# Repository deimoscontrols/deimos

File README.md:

# Deimos

|[Website](https://deimoscontrols.com) |\||[Control Program](https://github.com/deimoscontrols/deimos/tree/main/software/deimos) |\|| [Packet Formats](https://github.com/deimoscontrols/deimos/tree/main/software/deimos_shared) |\|| [Firmware](https://github.com/deimoscontrols/deimos/tree/main/firmware) |\|| [Hardware Designs](https://github.com/deimoscontrols/deimos/tree/main/hardware) |
|-----------------|-|--------------|-|----------|-|----------|-----|-|

Realtime data acquisition and controls ecosystem, including hardware, firmware, and software.

# Contact

|  | Purpose |
|-------|---------|
| support@deimoscontrols.com <br> or <br>https://deimoscontrols.com/contact/ | Questions about the hardware or software |

# Hardware Peripherals

| Model | I/O Medium | Sample/Control Rate | Input Capabilities | Output Capabilities |
|------|------------|------------|--------------------|---------------------|
| [Deimos DAQ 7.0.x](https://deimoscontrols.com/products/deimos_daq/) | UDP/IP/Ethernet | 5Hz-8kHz measure & control<br>5Hz-500Hz Modbus<br><br>Performance depends on network and host machine | 16x analog, 6x digital | 4x PWM <br>2x analog<br>4x GPIO |
| [Deimos DAQ 8.0.x](https://deimoscontrols.com/products/specs/) | UDP/IP and Modbus/TCP over Ethernet | 5Hz-8kHz measure & control<br>5Hz-500Hz Modbus<br><br>Performance depends on network and host machine | 6x voltage, 2x thermocouple, 3x resistance, 4x 4-20mA<br>2x GPIO, 4x encoder<br>Bus current, bus voltage, and board temperature diagnostics | 4x PWM<br>2x analog<br>4x GPIO |

# Controller Comm. Media

Communication with peripherals is done via message passing on an arbitrary socket. New communication media can be used by implementing the `Socket` trait.

While the controller can accommodate multiple communication media, a peripheral will typically only implement one method for reliability reasons.

| I/O Medium | Notes |
|------------|-------|
| UDP/IPV4 | Nominal peripheral I/O; compared to TCP, eliminates packet storm network instability.<br><br>The controller reasserts the full peripheral state on each cycle, so while UDP allows some packet loss (typically 1e-4 or less), a change in peripheral state is never missed permanently. |
| Unix socket | Inter-process communication option for software peripheral mockups |
| Thread channel | Inter-thread communication option for software peripheral mockups |

Several more socket implementations are planned, including TCP, UDP/IPV6, and thread channel message passing.

# Data Integrations

Data integration implementations perform I/O and database transactions on a separate core to avoid blocking the main control loop, unless no separate core is available.

| Target | I/O Medium | Notes |
|--------|--------|-------|
| CSV    | Disk | Fixed-width row format.<br>Wrap, split, or terminate at end of pre-sized file. |
| DataFrame | RAM | Wrap or terminate at end of preallocated in-memory storage. |
| TimescaleDB (postgres) | TCP or unix socket | Create table & schema or reuse existing.<br>Insert individual rows or write buffered batches for increased total ingestion rate.<br>Set fixed retention duration. |
| Latest-value | RAM | Read the latest data manually from outside the control program. |

# Calculation Functions

| Name | Description | Notes |
|------|-------------|-------|
| Controllers | | |
| SequenceMachine | A flexible state-machine where each state is defined by a time-dependent lookup table sequence with user-defined transition criteria | Allows implementation of essentially arbitrary scheduling and operational logic |
| Pid | Proportion-integral-derivative controller with anti-windup | |
| Hysteretic | Bang-bang controller with persistence counter | |
| Interpolation & Filtering | | |
| Butter | Second-order Butterworth low-pass filter | |
| Polynomial | Fast evaluation of polynomials for calibrations | Includes Levenberg-Marquardt curve-fitting utility |
| Temperature | | |
| TcKtype | K-type thermocouple tables with cold-junction correction | Highly-optimized, low-latency, embedded-compatible implementation based on ITS-90 tables |
| RtdPt100 | 100-ohm platinum RTD temperature-resistance tables | Highly-optimized, low-latency, embedded-compatible implementation based on DIN-43-760 / ITS-90 and IEC 60751 / Callender-Van Dusen |

... in addition to a variety of unremarkable math functions.

# Goals and Anti-Goals

The goals of this ecosystem are:

* Tightly-integrated sensor frontends
* _Fully independent_ input and output channels; every advertised channel is available _at the same time_
* Full reassertion of state at each control cycle; robust to packet loss
* SI-traceable calibrations
* Control program without required root/admin access or drivers
* Run on standard networking hardware with sub-microsecond time sync
* Semantic versioning for both hardware and software to prevent unexpected breaking changes
* 100% end-to-end open-source hardware, firmware, and software under permissive licenses

Notable anti-goals:

* Copyright mongering
* "Internet-of-Things" (IoT) functionality
* Over-the-Air (OTA) firmware updates
* Performative complexity
* Skimping on bits

# Versioning

To prevent unexpected breaking changes, both software and hardware use semantic versioning and, whenever possible, use procedural semver linting to avoid unexpected or unintuitive breakage.

Semantic versioning of hardware is not yet a well-established practice. Here, it is taken to cover both hardware and accompanying firmware, and their interfaces:

* Major version: Potentially breaking changes
    * Examples: Removing a channel, increasing filter phase lag, narrowing samplerate range, or changing packet interchange format, reducing overvoltage tolerance
        * Adding a channel is also a breaking change if it affects packet interchange format
    * Notable non-examples: Changing connector types for sensors without a noise-level or thermoelectric voltage sensitivity, changing model number
* Minor version: Backward-compatible changes
    * Examples: Adding a channel, increasing samplerate range, decreasing filter phase lag, increasing overvoltage tolerance
* Patch version: Forward- and backward- compatible changes
    * Examples: Updating silkscreen, changing non-sensitive connector types, swapping non-sensitive components such as decoupling capacitors

Both major and minor hardware versions are accompanied by new hardware project files. Patch hardware versions are applied to the existing hardware project files.

# License

Licensed under either of

* Apache License, Version 2.0, ([LICENSE-APACHE](LICENSE-APACHE.txt) or http://www.apache.org/licenses/LICENSE-2.0)
* MIT license ([LICENSE-MIT](LICENSE-MIT.txt) or http://opensource.org/licenses/MIT)

at your option.

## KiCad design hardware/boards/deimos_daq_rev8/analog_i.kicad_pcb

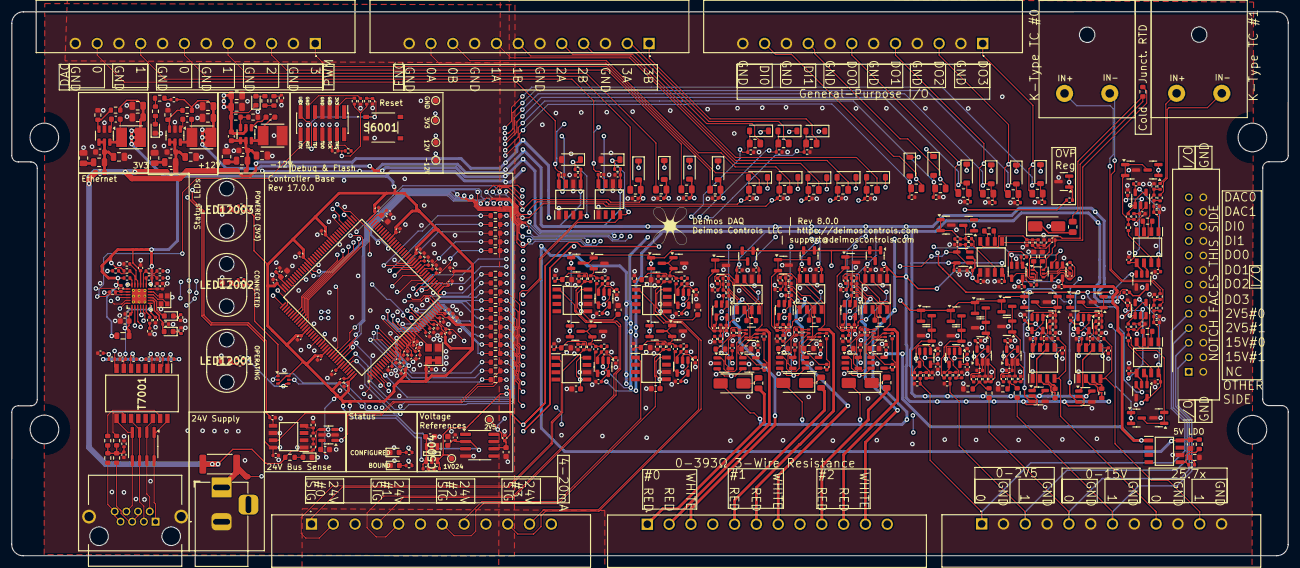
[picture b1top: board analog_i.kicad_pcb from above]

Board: 4 copper layers, 223.0 x 95.0 mm, 582 parts (0 on the bottom side), 312 nets.

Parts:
-1001: logo_minimal_25p4_by_20p3_mm; logo_minimal_12p7_by_10p9_mm
C3003, C10001, C10005, C11002, C11005, C14002, C14005, C14006, C28001, C30001, C32001, C34001: 0.1uF 50V 0603; C_0603_1608Metric
C4001, C4003, C5001, C5003, C9001, C9003, C13001, C13003, C15001, C15003, C17001, C17003: 2.2uF; C_0402_1005Metric
C4002, C5002, C9002, C13002, C15002, C17002: 1uF; C_0402_1005Metric
C4004, C4005, C4007, C4010, C5004, C5007, C5008, C5009, C5010, C6021, C6022, C6024, C6026, C6027, C6028, C6029, C6030, C6031, C6032, C6033, C6034, C6036, C6037, C6038, C6039, C6041, C6043, C6048, C6050, C7005, C7006, C7007, C7008, C7010, C7011, C8002, C8005, C9004, C9005, C13004, C13007, C13010, C15004, C15008, C15009, C16001, C17004, C17007, C17008, C17009, C17010, C18002, C19003, C19004, C21003, C21004, C23001, C24001, C24004, C26001, C27003, C27004, C29003, C29004, C31003, C31004, C33003, C33004, C35003, C35004, C36001, C36002, C37003, C37004, C38001, C38002, C39003, C39004, C41003, C41004, C43003, C43004, C45003, C45004, C47003, C47004, C53001, C53002, C54001, C54002: 0.1uF; C_0402_1005Metric
C4006, C4008, C6023, C6025, C9007, C9008, C11001, C14001, C18001, C22001, C23002, C23003, C26002, C26003: 10nF; C_0402_1005Metric
C5012, C6035, C6040, C6049, C6051, C7009: 10uF; C_0603_1608Metric
C6001, C6002, C6003, C6004, C6005, C6006, C6007, C6008, C6009, C6010, C6011, C6012, C6013, C6016, C6017, C6018, C6019, C6020, C7004: 1uF 0402; C_0402_1005Metric
C7003: 470pF 0402; C_0402_1005Metric
C7012: 4.7nF; C_0402_1005Metric
C8001: 0.1uF 0603; C_0603_1608Metric
C10002, C10003, C10004, C11003, C11004, C11007, C14003, C14004, C14008: 10uF 50V 0805; C_0805_2012Metric
C10006, C11006, C14007: 2.2uF 50V 0805; C_0805_2012Metric
C15005, C15007, C17005, C17006, C19001, C19002, C21001, C21002, C24002, C24003, C27001, C27002, C29001, C29002, C31001, C31002, C33001, C33002, C35001, C35002, C37001, C37002, C39001, C39002, C41001, C41002, C43001, C43002, C45001, C45002, C47001, C47002: 10nF C0G 5%; C_0402_1005Metric
D4001, D5001, D13001, D17001: D_Schottky; D_SMA
D6001, D6002, D6003, D6004, D7001, D7002, D12001, D12002, D12003, D12004: Purple LED; LED_0603_1608Metric
D7003: CDNBS08-SLVU2.8-4; SOIC-8_3.9x4.9mm_P1.27mm
D48001, D49001, D50001, D51001, D52001, D53002, D54002, D55002, D56001, D57001, D58001, D59001, D60001, D61001, D62001, D63001, D64001, D65001, D66001, D67001: B5819W SL; D_SOD-123
FB7001: GZ2012D601TF; L_0805_2012Metric
H2001, H2002, H3001, H3002: MountingHole_for_10-32; MountingHole_5mm
IC3002, IC17004, IC20001, IC24001, IC28001: BD42540FJ-CE2; SOIC127P600X175-8N
IC4001, IC5001, IC8001, IC9001, IC13001, IC15001, IC17001, IC36001, IC38001, IC53001, IC54001: INA826AIDR; SOIC127P600X175-8N
IC4002, IC4003, IC5002, IC5003, IC13002, IC13003, IC17002, IC17003: TLV333IDBVR; SOT-23-5
IC5004: REF35102QDBVR; SOT95P280X145-6N
IC6001: STM32H743ZIT6; QFP50P2200X2200X160-144N
IC10001, IC11001, IC14001: TPS560430XDBVR; SOT-23-6
J3001, J3002, J3003, J3004, J3005, J3006: WJ15EDGRM-3.81-12P
J3007: XG4C-2631; SHDR26W70P254_2X13_4030X820X900P
J6001: Conn_02x07_Odd_Even; PinHeader_2x07_P1.27mm_Vertical_SMD
J8001: Barrel_Jack PJ-202BH; BarrelJack_Horizontal
J9001, J15001: AM-K-PCB
J13001: RCH_RC01133; RCHRC01133
L10001: 12uH FNR4030S120MT; INDPM4040X300N
L10002, L11002, L14002: 220nH 0603; L_0603_1608Metric
L11001, L14001: 33uH FNR4020S330MT; INDPM4040X300N
LED12001, LED12002, LED12003: SMFLP10.0; SMFLP100
Q15001, Q15002, Q17001, Q17002, Q19001, Q19002, Q21001, Q21002, Q24001, Q24002, Q27001, Q27002, Q29001, Q29002, Q31001, Q31002, Q33001, Q33002, Q35001, Q35002, Q37001, Q37002, Q39001, Q39002, Q41001, Q41002, Q43001, Q43002, Q45001, Q45002, Q47001, Q47002: MMBFJ113; SOT-23
R3001: PTS060301B100RP100; R_0603_1608Metric
R3002, R11004, R12001, R14005: 243k 0603; R_0603_1608Metric
R3003, R17001, R17007, R19001, R19002, R37001, R37002, R39001, R39002: 10k 1%; R_0402_1005Metric
R3004, R10002: 51k 0603; R_0603_1608Metric
R3005, R21001, R21002, R24001, R24002, R27001, R27002, R29001, R29002, R31001, R31002, R33001, R33002, R35001, R35002, R41001, R41002, R43001, R43002, R45001, R45002, R47001, R47002, R53001, R54001: 3.3k 1%; R_0402_1005Metric
R4001, R4007, R9004, R9006, R23001, R23002, R26001, R26002: 10k 1%; C_0402_1005Metric
R4002, R5002, R9005, R13002, R15005, R17002, R36001, R38001, R40002, R42002: RNCF0603TKY2K00 2k 0.01% 5ppm/C; R_0603_1608Metric
R4003, R5003, R13003, R17003: 300; R_0805_2012Metric
R4004, R4005, R5004, R5005, R13004, R13005, R17004, R17005: 10; C_0402_1005Metric
R4006, R4009, R5006, R5009, R13006, R13009, R17006, R17009, R40001, R42001: RNCF0603TKW10K0 10k 0.01% 5ppm/C; R_0603_1608Metric
R6001, R6002, R6003, R6004, R6005, R6006, R6007, R6008, R6009, R6010, R6011, R6012, R6013, R6016, R6017, R6018, R6019, R6020: 10R 0603; R_0603_1608Metric
R6021, R6022, R6028, R6029, R6030, R7002, R7004, R7006, R7009, R7010, R7012, R7019, R8006, R8007, R12002, R12005: 10k; R_0402_1005Metric
R6024, R12008, R12009, R12010, R12011, R12012, R12013, R13007: 100R 0402; R_0402_1005Metric
R6025, R6026: 1k; R_0402_1005Metric
R7001, R7003, R7005, R7007: 33R; R_0402_1005Metric
R7008, R7015, R8005: 1.5k; R_0402_1005Metric
R7011, R7013, R7016, R7018: 49.9; R_0402_1005Metric
R7014: 12k; R_0402_1005Metric
R7017: 100R; R_0402_1005Metric
R7020, R7021, R7022, R7023: 75; R_0603_1608Metric
R7024, R9003, R15003, R28001, R30001, R32001, R34001, R36002, R38002, R44001, R46001, R48002, R49002, R50002, R51002, R52002, R53003, R54003, R55001, R55004, R56001, R57001, R58001, R59001, R60001, R61001, R64001, R65002, R66002: 1M; R_0402_1005Metric
R8004: MRF6432(2512)LR006FTS 0.006 1%; R_2512_6332Metric
R9001, R9002, R15001, R15002: 10; R_0402_1005Metric
R10001, R11005, R12003, R12004, R12006, R12007, R14004: 22.1k 0603; R_0603_1608Metric
R10003, R11003, R14003: 1R 0805; R_0805_2012Metric
R11001, R14001, R18001, R22001: 200R; R_0402_1005Metric
R11002, R14002, R18002, R22002: RNCF0603TKY75R0 75R 0.01% 5ppm/C; R_0603_1608Metric
R15004, R15006: 100k 1%; R_0402_1005Metric
R48001, R49001, R50001, R51001, R52001, R53002, R54002, R55003, R65001, R66001: 22k; R_0805_2012Metric
R55002, R56002, R57002, R58002, R59002, R60002, R61002, R64002: 49.9; R_0805_2012Metric
S6001: TS-1187A-B-A-B; TS1187ABAB
T7001: H1102NLT; SOIC127P940X622-16N
TP7001, TP7002: TestPoint_+12V; TestPoint_Pad_D1.0mm
TP7003: TestPoint_+2V5; TestPoint_Pad_D1.0mm
TP7004: TestPoint_+3V3; TestPoint_Pad_D1.0mm
TP7005: TestPoint_+1V024; TestPoint_Pad_D1.0mm
TP8002: TestPoint_GND_1; TestPoint_Pad_D1.0mm
U3001: ATL431BQDBZR; SOT-23
U4001, U5001, U12001, U13001, U17001: NTJD4001NT1G; SOT-363_SC-70-6
U6002: ADR4525; SOIC-8_3.9x4.9mm_P1.27mm
U7001: LAN8742A; VQFN-24-1EP_4x4mm_P0.5mm_EP2.5x2.5mm_ThermalVias
U8001: INA181A2; SOT-23-6
U15001, U16001, U17002, U18001, U19001, U21001, U24001, U27001, U29001, U31001, U33001, U35001, U36001, U37001, U38001, U39001, U41001, U43001, U45001, U47001: OPA196xDBV; SOT-23-5
Y6001: SiT1602BI-21-33S-48.000000; Crystal_SMD_3225-4Pin_3.2x2.5mm
Y7001: NX2016SA-25.000M-STD-CZS-1; Crystal_SMD_2016-4Pin_2.0x1.6mm

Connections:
2V5_OVP: Q15001.1 (D), Q15001.2 (S), Q17001.1 (D), Q17001.2 (S), Q19001.1 (D), Q19001.2 (S), Q21001.1 (D), Q21001.2 (S), Q24001.1 (D), Q24001.2 (S), Q27001.1 (D), Q27001.2 (S), Q29001.1 (D), Q29001.2 (S), Q31001.1 (D), Q31001.2 (S), Q33001.1 (D), Q33001.2 (S), Q35001.1 (D), Q35001.2 (S), Q37001.1 (D), Q37001.2 (S), Q39001.1 (D), Q39001.2 (S), Q41001.1 (D), Q41001.2 (S), Q43001.1 (D), Q43001.2 (S), Q45001.1 (D), Q45001.2 (S), Q47001.1 (D), Q47001.2 (S), R3005.1, U3001.1 (K), U3001.2 (REF)
+1V024: C5008.1, IC5004.6 (VREF), TP7005.1, U16001.3 (+), U18001.3 (+), U36001.3 (+), U38001.3 (+)
+2V5: C6023.2, C6024.2, C6050.2, C6051.2, IC4002.3 (+IN), IC4003.3 (+IN), IC5002.3 (+IN), IC5003.3 (+IN), IC6001.32 (VREF+), IC13002.3 (+IN), IC13003.3 (+IN), IC17002.3 (+IN), IC17003.3 (+IN), TP7003.1, U6002.6 (OUT)
+3V3: C5009.2, C5012.2, C6021.2, C6022.2, C6025.2, C6026.2, C6028.2, C6029.2, C6030.2, C6031.2, C6032.2, C6033.2, C6036.2, C6037.2, C6038.2, C6039.2, C6043.2, C6048.2, C6049.2, C7005.2, C8001.1, C10003.1, C10006.1, D4001.2 (A), D5001.2 (A), D13001.2 (A), D17001.2 (A), D48001.1 (K), D49001.1 (K), D50001.1 (K), D51001.1 (K), D52001.1 (K), D53002.1 (K), D54002.1 (K), D55002.1 (K), D58001.1 (K), D59001.1 (K), D60001.1 (K), D61001.1 (K), D62001.1 (K), D63001.1 (K), D64001.1 (K), D65001.1 (K), D66001.1 (K), D67001.1 (K), FB7001.1, IC5004.3 (EN), IC5004.4 (VIN), IC6001.17 (VDD_1), IC6001.30 (VDD_2), IC6001.33 (VDDA), IC6001.39 (VDD_3), IC6001.52 (VDD_4), IC6001.62 (VDD_5), IC6001.72 (VDD_6), IC6001.84 (VDD_7), IC6001.95 (VDD33USB), IC6001.108 (VDD_8), IC6001.121 (VDD_9), IC6001.131 (VDD_10), IC6001.144 (VDD_11), L10001.1, R3005.2, R6021.1, R6028.1, R6029.2, R6030.2, R7002.1, R7004.1, R7006.1, R7008.2, R7009.1, R10002.1, R12008.1, R13007.1, TP7004.1, U6002.2 (IN), U7001.9 (VDDIO), U8001.6 (V+), U12001.3 (D2), U12001.6 (D1), Y6001.1 (OE/~ST/NC), Y6001.4 (VDD)
+5V: C4007.1, C4010.1, C5007.1, C5010.1, C13007.1, C13010.1, C17007.1, C17010.1, IC3002.1 (VO), IC4002.5 (V+), IC4003.5 (V+), IC5002.5 (V+), IC5003.5 (V+), IC13002.5 (V+), IC13003.5 (V+), IC17002.5 (V+), IC17003.5 (V+)
+12V: C4004.1, C5004.1, C8005.2, C9004.1, C11006.1, C11007.1, C13004.1, C15004.1, C15008.2, C17004.1, C17008.2, C19003.2, C21003.2, C24001.2, C27003.2, C29003.2, C31003.2, C33003.2, C35003.2, C36001.2, C37003.2, C38001.2, C39003.2, C41003.2, C43003.2, C45003.2, C47003.2, C53001.2, C54001.2, IC4001.8 (+VS), IC5001.8 (+VS), IC8001.8 (+VS), IC9001.8 (+VS), IC13001.8 (+VS), IC15001.8 (+VS), IC17001.8 (+VS), IC36001.8 (+VS), IC38001.8 (+VS), IC53001.8 (+VS), IC54001.8 (+VS), L11001.1, R11004.1, R12005.2, TP7001.1, U15001.5 (V+), U16001.5 (V+), U17002.5 (V+), U18001.5 (V+), U19001.5 (V+), U21001.5 (V+), U24001.5 (V+), U27001.5 (V+), U29001.5 (V+), U31001.5 (V+), U33001.5 (V+), U35001.5 (V+), U36001.5 (V+), U37001.5 (V+), U38001.5 (V+), U39001.5 (V+), U41001.5 (V+), U43001.5 (V+), U45001.5 (V+), U47001.5 (V+)
+24V: C3003.2, C28001.2, C30001.2, C32001.2, C34001.2, IC3002.8 (VCC), IC17004.5 (ADJ_/_EN), IC17004.8 (VCC), IC20001.5 (ADJ_/_EN), IC20001.8 (VCC), IC24001.5 (ADJ_/_EN), IC24001.8 (VCC), IC28001.5 (ADJ_/_EN), IC28001.8 (VCC), L10002.2, L11002.2, L14002.2, R3002.2, R8004.1, R8006.1, R12001.2, U8001.4 (-)
-12V: C4005.1, C8002.2, C9005.1, C14005.1, C14007.1, C14008.1, C15009.2, C16001.2, C17009.2, C18002.2, C19004.2, C21004.2, C23001.1, C24004.2, C26001.1, C27004.2, C29004.2, C31004.2, C33004.2, C35004.2, C36002.2, C37004.2, C38002.2, C39004.2, C41004.2, C43004.2, C45004.2, C47004.2, C53002.2, C54002.2, D12002.1 (K), IC4001.5 (-VS), IC5001.5 (-VS), IC8001.5 (-VS), IC9001.5 (-VS), IC13001.5 (-VS), IC14001.2 (GND), IC15001.5 (-VS), IC17001.5 (-VS), IC36001.5 (-VS), IC38001.5 (-VS), IC53001.5 (-VS), IC54001.5 (-VS), R14004.2, R53001.1, R54001.1, TP7002.1, U15001.2 (V-), U16001.2 (V-), U17002.2 (V-), U18001.2 (V-), U19001.2 (V-), U21001.2 (V-), U24001.2 (V-), U27001.2 (V-), U29001.2 (V-), U31001.2 (V-), U33001.2 (V-), U35001.2 (V-), U36001.2 (V-), U37001.2 (V-), U38001.2 (V-), U39001.2 (V-), U41001.2 (V-), U43001.2 (V-), U45001.2 (V-), U47001.2 (V-)
/analog_frontend/2p5V_0: J3003.1, J3007.9, R46001.1, R47001.1
/analog_frontend/2p5V_1: J3003.3, J3007.7, R44001.1, R45001.1
/analog_frontend/4-20mA Frontend1/+24_EXC: IC20001.1 (VO), J3002.5
/analog_frontend/4-20mA Frontend1/SIGNAL: J3002.4, R14001.2, R14002.2, R32001.1, R33001.1
/analog_frontend/4-20mA Frontend2/+24_EXC: IC24001.1 (VO), J3002.8
/analog_frontend/4-20mA Frontend2/SIGNAL: J3002.7, R18001.2, R18002.2, R30001.1, R31001.1
/analog_frontend/4-20mA Frontend3/+24_EXC: IC28001.1 (VO), J3002.11
/analog_frontend/4-20mA Frontend3/SIGNAL: J3002.10, R22001.2, R22002.2, R28001.1, R29001.1
/analog_frontend/4-20mA Frontend/+24_EXC: IC17004.1 (VO), J3002.2
/analog_frontend/4-20mA Frontend/SIGNAL: J3002.1, R11001.2, R11002.2, R34001.1, R35001.1
/analog_frontend/15V_0: J3003.5, J3007.5, R42001.2
/analog_frontend/15V_1: J3003.7, J3007.3, R40001.2
/analog_frontend/25p7x_0: IC38001.4 (+IN), J3003.9, R38002.1
/analog_frontend/25p7x_1: IC36001.4 (+IN), J3003.11, R36002.1
/analog_frontend/AIN2: C15007.2, R6003.1, U15001.1, U15001.4 (-)
/analog_frontend/AIN3: C35002.2, R6007.1, U35001.1, U35001.4 (-)
/analog_frontend/AIN4: C33002.2, R6008.1, U33001.1, U33001.4 (-)
/analog_frontend/AIN5: C31002.2, R6004.1, U31001.1, U31001.4 (-)
/analog_frontend/AIN6: C29002.2, R6005.1, U29001.1, U29001.4 (-)
/analog_frontend/AIN7: C21002.2, R6006.1, U21001.1, U21001.4 (-)
/analog_frontend/AIN8: C24003.2, R6009.1, U24001.1, U24001.4 (-)
/analog_frontend/AIN9: C27002.2, R6010.1, U27001.1, U27001.4 (-)
/analog_frontend/AIN10: C17006.2, R6011.1, U17002.1, U17002.4 (-)
/analog_frontend/AIN11: C19002.2, R6012.1, U19001.1, U19001.4 (-)
/analog_frontend/AIN12: C47002.2, R6013.1, U47001.1, U47001.4 (-)
/analog_frontend/AIN13_DAC0: D56001.1 (K), IC6001.40 (PA4), IC53001.4 (+IN), R53001.2
/analog_frontend/AIN14_DAC1: D57001.1 (K), IC6001.41 (PA5), IC54001.4 (+IN), R54001.2
/analog_frontend/AIN15: C45002.2, R6016.1, U45001.1, U45001.4 (-)
/analog_frontend/AIN16: C43002.2, R6017.1, U43001.1, U43001.4 (-)
/analog_frontend/AIN17: C41002.2, R6018.1, U41001.1, U41001.4 (-)
/analog_frontend/AIN18: C39002.2, R6019.1, U39001.1, U39001.4 (-)
/analog_frontend/AIN19: C37002.2, R6020.1, U37001.1, U37001.4 (-)
/analog_frontend/DAC0: IC53001.7 (VOUT), J3005.11, J3007.25
/analog_frontend/DAC1: IC54001.7 (VOUT), J3005.9, J3007.23
/analog_frontend/DI0: D65001.2 (A), IC6001.114 (PD0), R65001.2, R65002.1
/analog_frontend/DI0_CONN: J3006.11, J3007.21, R65001.1
/analog_frontend/DI1: D66001.2 (A), IC6001.115 (PD1), R66001.2, R66002.1
/analog_frontend/DI1_CONN: J3006.9, J3007.19, R66001.1
/analog_frontend/DO0: D67001.2 (A), IC6001.116 (PD2), R64001.1, R64002.1
/analog_frontend/DO0_CONN: J3006.7, J3007.17, R64002.2
/analog_frontend/DO1: D62001.2 (A), IC6001.117 (PD3), R59001.1, R59002.1
/analog_frontend/DO1_CONN: J3006.5, J3007.15, R59002.2
/analog_frontend/DO2: D63001.2 (A), IC6001.118 (PD4), R60001.1, R60002.1
/analog_frontend/DO2_CONN: J3006.3, J3007.13, R60002.2
/analog_frontend/DO3: D64001.2 (A), IC6001.119 (PD5), R61001.1, R61002.1
/analog_frontend/DO3_CONN: J3006.1, J3007.11, R61002.2
/analog_frontend/ENCODER0_A: D48001.2 (A), IC6001.60 (PE9), R48001.2, R48002.1
/analog_frontend/ENCODER0_B: D49001.2 (A), IC6001.64 (PE11), R49001.2, R49002.1
/analog_frontend/ENCODER1_A: D50001.2 (A), IC6001.96 (PC6), R50001.2, R50002.1
/analog_frontend/ENCODER1_B: D51001.2 (A), IC6001.97 (PC7), R51001.2, R51002.1
/analog_frontend/ENCODER2_A: D52001.2 (A), IC6001.136 (PB6), R52001.2, R52002.1
/analog_frontend/ENCODER2_B: D53002.2 (A), IC6001.137 (PB7), R53002.2, R53003.1
/analog_frontend/ENCODER3_A: D54002.2 (A), IC6001.134 (PB4), R54002.2, R54003.1
/analog_frontend/ENCODER3_B: D55002.2 (A), IC6001.135 (PB5), R55003.2, R55004.1
/analog_frontend/K-Type TC Amp1/Signal+: C15001.1, C15002.1, IC15001.4 (+IN), R15001.2
/analog_frontend/K-Type TC Amp1/Signal-: C15002.2, C15003.1, IC15001.1 (-IN1), R15002.1, R15003.1
/analog_frontend/K-Type TC Amp1/sallen_key_1kHz/VIN: IC15001.7 (VOUT), R19001.1
/analog_frontend/K-Type TC Amp/Signal+: C9001.1, C9002.1, IC9001.4 (+IN), R9001.2
/analog_frontend/K-Type TC Amp/Signal-: C9002.2, C9003.1, IC9001.1 (-IN1), R9002.1, R9003.1
/analog_frontend/K-Type TC Amp/sallen_key_1kHz/VIN: IC9001.7 (VOUT), R17001.1
/analog_frontend/PWM0: D58001.2 (A), IC6001.5 (PE6), R55001.1, R55002.1
/analog_frontend/PWM1: D59001.2 (A), IC6001.75 (PB14), R56001.1, R56002.1
/analog_frontend/PWM2: D60001.2 (A), IC6001.139 (PB8), R57001.1, R57002.1
/analog_frontend/PWM3: D61001.2 (A), IC6001.140 (PB9), R58001.1, R58002.1
/analog_frontend/RTD Amp1/R+: J3001.5, R13003.2
/analog_frontend/RTD Amp1/R-: J3001.6, R13004.2, U13001.3 (D2)
/analog_frontend/RTD Amp1/W-: J3001.7, R13005.2, U13001.6 (D1)
/analog_frontend/RTD Amp1/rtd_amp_inner/Signal+: C13001.2, C13002.1, IC13001.4 (+IN), R13004.1
/analog_frontend/RTD Amp1/rtd_amp_inner/Signal-: C13002.2, C13003.1, IC13001.1 (-IN1), R13005.1
/analog_frontend/RTD Amp1/rtd_amp_inner/Vout: IC13001.7 (VOUT), R24001.1
/analog_frontend/RTD Amp2/R+: J3001.9, R17003.2
/analog_frontend/RTD Amp2/R-: J3001.10, R17004.2, U17001.3 (D2)
/analog_frontend/RTD Amp2/W-: J3001.11, R17005.2, U17001.6 (D1)
/analog_frontend/RTD Amp2/rtd_amp_inner/Signal+: C17001.2, C17002.1, IC17001.4 (+IN), R17004.1
/analog_frontend/RTD Amp2/rtd_amp_inner/Signal-: C17002.2, C17003.1, IC17001.1 (-IN1), R17005.1
/analog_frontend/RTD Amp2/rtd_amp_inner/Vout: IC17001.7 (VOUT), R27001.1
/analog_frontend/RTD Amp/R+: J3001.1, R5003.2
/analog_frontend/RTD Amp/R-: J3001.2, R5004.2, U5001.3 (D2)
/analog_frontend/RTD Amp/W-: J3001.3, R5005.2, U5001.6 (D1)
/analog_frontend/RTD Amp/rtd_amp_inner/Signal+: C5001.2, C5002.1, IC5001.4 (+IN), R5004.1
/analog_frontend/RTD Amp/rtd_amp_inner/Signal-: C5002.2, C5003.1, IC5001.1 (-IN1), R5005.1
/analog_frontend/RTD Amp/rtd_amp_inner/Vout: IC5001.7 (VOUT), R21001.1
/analog_frontend/ain_0-15V_1/sallen_key_3kHz8/VIN: R40001.1, R40002.1, R41001.1
/analog_frontend/ain_0-15V_/sallen_key_3kHz8/VIN: R42001.1, R42002.1, R43001.1
/analog_frontend/ain_g25p7_1/sallen_key_1kHz2/VIN: IC36001.7 (VOUT), R37001.1
/analog_frontend/ain_g25p7_/sallen_key_1kHz2/VIN: IC38001.7 (VOUT), R39001.1
/analog_frontend/pwm_in_buf1/VIN: J3004.11, R48001.1
/analog_frontend/pwm_in_buf2/VIN: J3004.5, R52001.1
/analog_frontend/pwm_in_buf3/VIN: J3004.7, R51001.1
/analog_frontend/pwm_in_buf4/VIN: J3004.8, R50001.1
/analog_frontend/pwm_in_buf5/VIN: J3004.4, R53002.1
/analog_frontend/pwm_in_buf8/VIN: J3004.2, R54002.1
/analog_frontend/pwm_in_buf9/VIN: J3004.1, R55003.1
/analog_frontend/pwm_in_buf/VIN: J3004.10, R49001.1
/analog_frontend/pwm_out_buf1/VOUT: J3005.5, R56002.2
/analog_frontend/pwm_out_buf2/VOUT: J3005.3, R57002.2
/analog_frontend/pwm_out_buf3/VOUT: J3005.1, R58002.2
/analog_frontend/pwm_out_buf/VOUT: J3005.7, R55002.2
/analog_frontend/rtd_amp_inner1/250uA_SINK_1: R3001.1, R4005.2, U4001.6 (D1)
/analog_frontend/rtd_amp_inner1/250uA_SINK_2: R3001.2, R4003.2, R4004.2, U4001.3 (D2)
/analog_frontend/rtd_amp_inner1/Signal+: C4001.2, C4002.1, IC4001.4 (+IN), R4004.1
/analog_frontend/rtd_amp_inner1/Signal-: C4002.2, C4003.1, IC4001.1 (-IN1), R4005.1
/analog_frontend/rtd_amp_inner1/Vout: IC4001.7 (VOUT), R15004.2
/base/AIN0: R6001.1, U8001.1
/base/AIN1: IC8001.7 (VOUT), R6002.1
/base/Micro/AIN0_Filt: C6001.1, IC6001.13 (PF3), R6001.2
/base/Micro/AIN1_Filt: C6002.1, IC6001.14 (PF4), R6002.2
/base/Micro/AIN2_Filt: C6003.1, IC6001.15 (PF5), R6003.2
/base/Micro/AIN3_Filt: C6007.1, IC6001.18 (PF6), R6007.2
/base/Micro/AIN4_Filt: C6008.1, IC6001.19 (PF7), R6008.2
/base/Micro/AIN5_Filt: C6004.1, IC6001.20 (PF8), R6004.2
/base/Micro/AIN6_Filt: C6005.1, IC6001.21 (PF9), R6005.2
/base/Micro/AIN7_Filt: C6006.1, IC6001.22 (PF10), R6006.2
/base/Micro/AIN8_Filt: C6009.1, IC6001.26 (PC0), R6009.2
/base/Micro/AIN9_Filt: C6010.1, IC6001.28 (PC2_C), R6010.2
/base/Micro/AIN10_Filt: C6011.1, IC6001.29 (PC3_C), R6011.2
/base/Micro/AIN11_Filt: C6012.1, IC6001.34 (PA0), R6012.2
/base/Micro/AIN12_Filt: C6013.1, IC6001.37 (PA3), R6013.2
/base/Micro/AIN15_Filt: C6016.1, IC6001.42 (PA6), R6016.2
/base/Micro/AIN16_Filt: C6017.1, IC6001.46 (PB0), R6017.2
/base/Micro/AIN17_Filt: C6018.1, IC6001.47 (PB1), R6018.2
/base/Micro/AIN18_Filt: C6019.1, IC6001.49 (PF11), R6019.2
/base/Micro/AIN19_Filt: C6020.1, IC6001.50 (PF12), R6020.2
/base/Micro/DEBUG_RESET: C6027.2, IC6001.25 (NRST), J6001.12, R6028.2, S6001.A1 (COM_1), U7001.15 (~RST)
/base/Micro/DEBUG_TCK/SWCLK: IC6001.109 (PA14), J6001.6, R6030.1
/base/Micro/DEBUG_TDI: IC6001.110 (PA15), J6001.10
/base/Micro/DEBUG_TDO/SWO: IC6001.133 (PB3), J6001.8
/base/Micro/DEBUG_TMS/SWDIO: IC6001.105 (PA13), J6001.4, R6029.1
/base/Micro/Ethernet/RX+: R7013.1, T7001.6 (RD+), U7001.23 (RXP)
/base/Micro/Ethernet/RX-: R7011.1, T7001.8 (RD-), U7001.22 (RXN)
/base/Micro/Ethernet/TX+: R7018.1, T7001.1 (TD+), U7001.21 (TXP)
/base/Micro/Ethernet/TX-: R7016.1, T7001.3 (TD-), U7001.20 (TXN)
/base/Micro/HSECLK: IC6001.23 (PH0-OSC_IN), Y6001.3 (OUT)
/base/Micro/LED0: IC6001.4 (PE5), U12001.2 (G1)
/base/Micro/LED1: IC6001.3 (PE4), R6025.2
/base/Micro/LED2: IC6001.2 (PE3), R6026.2
/base/Micro/LED3: IC6001.1 (PE2), U12001.5 (G2)
/base/Micro/RMII_CRS_DV: IC6001.43 (PA7), R7005.1
/base/Micro/RMII_MDC: IC6001.27 (PC1), U7001.13 (MDC)
/base/Micro/RMII_MDIO: IC6001.36 (PA2), R7008.1, U7001.12 (MDIO)
/base/Micro/RMII_REF_CLK: IC6001.35 (PA1), R7007.2
/base/Micro/RMII_RXD0: IC6001.44 (PC4), R7001.2
/base/Micro/RMII_RXD1: IC6001.45 (PC5), R7003.2
/base/Micro/RMII_TXD0: IC6001.128 (PG13), U7001.17 (TXD0)
/base/Micro/RMII_TXD1: IC6001.74 (PB13), U7001.18 (TXD1)
/base/Micro/RMII_TX_EN: IC6001.126 (PG11), U7001.16 (TXEN)
/base/Micro/UART_RX: IC6001.78 (PD9), J6001.13
/base/Micro/UART_TX: IC6001.77 (PD8), J6001.14
GND: C3003.1, C4001.1, C4003.2, C4004.2, C4005.2, C4007.2, C4010.2, C5001.1, C5003.2, C5004.2, C5007.2, C5008.2, C5009.1, C5010.2, C5012.1, C6001.2, C6002.2, C6003.2, C6004.2, C6005.2, C6006.2, C6007.2, C6008.2, C6009.2, C6010.2, C6011.2, C6012.2, C6013.2, C6016.2, C6017.2, C6018.2, C6019.2, C6020.2, C6021.1, C6022.1, C6023.1, C6024.1, C6025.1, C6026.1, C6027.1, C6028.1, C6029.1, C6030.1, C6031.1, C6032.1, C6033.1, C6034.1, C6035.1, C6036.1, C6037.1, C6038.1, C6039.1, C6040.2, C6041.1, C6043.1, C6048.1, C6049.1, C6050.1, C6051.1, C7003.1, C7004.1, C7005.1, C7006.1, C7007.1, C7008.1, C7009.1, C7010.1, C7011.1, C7012.2, C8001.2, C8002.1, C8005.1, C9001.2, C9003.2, C9004.2, C9005.2, C10002.2, C10003.2, C10005.2, C10006.2, C11001.2, C11002.2, C11004.2, C11006.2, C11007.2, C13001.1, C13003.2, C13004.2, C13007.2, C13010.2, C14001.2, C14002.2, C14004.2, C14007.2, C14008.2, C15001.2, C15003.2, C15004.2, C15005.1, C15008.1, C15009.1, C16001.1, C17001.1, C17003.2, C17004.2, C17005.1, C17007.2, C17008.1, C17009.1, C17010.2, C18001.2, C18002.1, C19001.1, C19003.1, C19004.1, C21001.1, C21003.1, C21004.1, C22001.2, C23001.2, C24001.1, C24002.1, C24004.1, C26001.2, C27001.1, C27003.1, C27004.1, C28001.1, C29001.1, C29003.1, C29004.1, C30001.1, C31001.1, C31003.1, C31004.1, C32001.1, C33001.1, C33003.1, C33004.1, C34001.1, C35001.1, C35003.1, C35004.1, C36001.1, C36002.1, C37001.1, C37003.1, C37004.1, C38001.1, C38002.1, C39001.1, C39003.1, C39004.1, C41001.1, C41003.1, C41004.1, C43001.1, C43003.1, C43004.1, C45001.1, C45003.1, C45004.1, C47001.1, C47003.1, C47004.1, C53001.1, C53002.1, C54001.1, C54002.1, D6001.1 (K), D6002.1 (K), D6003.1 (K), D6004.1 (K), D12001.1 (K), D12003.1 (K), D12004.1 (K), D56001.2 (A), D57001.2 (A), IC3002.6 (GND), IC4001.6 (REF), IC4002.2 (V-), IC4003.2 (V-), IC5001.6 (REF), IC5002.2 (V-), IC5003.2 (V-), IC5004.1 (GND_1), IC5004.2 (GND_2), IC6001.16 (VSS_1), IC6001.31 (VSSA), IC6001.38 (VSS_2), IC6001.51 (VSS_3), IC6001.61 (VSS_4), IC6001.83 (VSS_5), IC6001.94 (VSS_6), IC6001.107 (VSS_7), IC6001.120 (VSS_8), IC6001.130 (VSS_9), IC8001.1 (-IN1), IC8001.6 (REF), IC10001.2 (GND), IC11001.2 (GND), IC13001.6 (REF), IC13002.2 (V-), IC13003.2 (V-), IC17001.6 (REF), IC17002.2 (V-), IC17003.2 (V-), IC17004.6 (GND), IC20001.6 (GND), IC24001.6 (GND), IC28001.6 (GND), IC36001.1 (-IN1), IC38001.1 (-IN1), IC53001.1 (-IN1), IC53001.6 (REF), IC54001.1 (-IN1), IC54001.6 (REF), J3003.2, J3003.4, J3003.6, J3003.8, J3003.10, J3003.12, J3004.3, J3004.6, J3004.9, J3004.12, J3005.2, J3005.4, J3005.6, J3005.8, J3005.10, J3005.12, J3006.2, J3006.4, J3006.6, J3006.8, J3006.10, J3006.12, J3007.2, J3007.4, J3007.6, J3007.8, J3007.10, J3007.12, J3007.14, J3007.16, J3007.18, J3007.20, J3007.22, J3007.24, J3007.26, J6001.5, J6001.7, J8001.2, J13001.9 (MH1), J13001.10 (MH2), L14001.2, Q15002.3 (G), Q17002.3 (G), Q19002.3 (G), Q21002.3 (G), Q24002.3 (G), Q27002.3 (G), Q29002.3 (G), Q31002.3 (G), Q33002.3 (G), Q35002.3 (G), Q37002.3 (G), Q39002.3 (G), Q41002.3 (G), Q43002.3 (G), Q45002.3 (G), Q47002.3 (G), R3004.1, R4006.2, R4009.2, R5006.2, R5009.2, R6022.2, R6024.1, R7010.1, R7012.2, R7015.1, R7017.1, R7019.2, R7024.2, R8005.1, R9003.2, R10001.2, R10003.2, R11002.1, R11003.2, R11005.2, R12002.2, R13006.2, R13009.2, R14002.1, R14003.2, R14005.1, R15003.2, R17006.2, R17009.2, R18002.1, R22002.1, R28001.2, R30001.2, R32001.2, R34001.2, R36002.2, R38002.2, R40002.2, R42002.2, R44001.2, R46001.2, R48002.2, R49002.2, R50002.2, R51002.2, R52002.2, R53003.2, R54003.2, R55001.2, R55004.2, R56001.2, R57001.2, R58001.2, R59001.2, R60001.2, R61001.2, R64001.2, R65002.2, R66002.2, S6001.C1 (NO_1), TP8002.1, U3001.3 (A), U6002.4 (GND), U7001.25 (VSS), U8001.2 (GND), U8001.5 (REF), U16001.4 (-), U18001.4 (-), U36001.4 (-), U38001.4 (-), Y6001.2 (GND), Y7001.2 (GND_1), Y7001.4 (GND_2)
unnamed: C7012.1, R7020.2, R7021.1, R7022.1, R7023.2, R7024.1
unnamed: C10004.2, R10003.1
unnamed: C11001.1, R11001.1
unnamed: C11003.2, R11003.1
unnamed: C14001.1, R14001.1
unnamed: C14003.2, R14003.1
unnamed: C18001.1, R18001.1
unnamed: C22001.1, R22001.1
unnamed: D4001.1 (K), R4003.1
unnamed: D5001.1 (K), R5003.1
unnamed: D6001.2 (A), R12011.2
unnamed: D6002.2 (A), R6025.1
unnamed: D6003.2 (A), R6026.1
unnamed: D6004.2 (A), R12013.2
unnamed: D7001.2 (A), R7012.1, U7001.2 (LED2/~INTSEL)
unnamed: D7001.1 (K), R7015.2
unnamed: D7002.2 (A), U7001.3 (LED1/REGOFF)
unnamed: D7002.1 (K), R7019.1
unnamed: D12001.2 (A), R12001.1
unnamed: D12002.2 (A), R12004.1
unnamed: D12003.2 (A), R12007.1
unnamed: D12004.2 (A), R12009.2
unnamed: D13001.1 (K), R13003.1
unnamed: D17001.1 (K), R17003.1
unnamed: IC3002.5 (ADJ_/_EN), R3002.1, R3003.1
unnamed: IC4001.2 (RG_1), R4002.1
unnamed: IC4001.3 (RG_2), R4002.2
unnamed: C4006.1, IC4002.4 (-IN), R4001.2
unnamed: C4006.2, IC4002.1 (OUT), U4001.2 (G1)
unnamed: C4008.1, IC4003.4 (-IN), R4007.1
unnamed: C4008.2, IC4003.1 (OUT), U4001.5 (G2)
unnamed: IC5001.2 (RG_1), R5002.1
unnamed: IC5001.3 (RG_2), R5002.2
unnamed: C9007.1, IC5002.4 (-IN), R9004.2
unnamed: C9007.2, IC5002.1 (OUT), U5001.2 (G1)
unnamed: C9008.1, IC5003.4 (-IN), R9006.1
unnamed: C9008.2, IC5003.1 (OUT), U5001.5 (G2)
unnamed: IC6001.138 (BOOT0), R6022.1
unnamed: IC6001.143 (PDR_ON), R6021.2
unnamed: C6034.2, C6035.2, IC6001.71 (VCAP_1)
unnamed: C6040.1, C6041.2, IC6001.106 (VCAP_2)
unnamed: IC8001.4 (+IN), R8005.2, R8007.1
unnamed: IC9001.6 (REF), U16001.1
unnamed: IC9001.2 (RG_1), R9005.1
unnamed: IC9001.3 (RG_2), R9005.2
unnamed: C10001.2, IC10001.1 (CB)
unnamed: C10002.1, C10004.1, C10005.1, IC10001.4 (EN), IC10001.5 (VIN), L10002.1
unnamed: IC10001.3 (FB), R10001.1, R10002.2
unnamed: C10001.1, IC10001.6 (SW), L10001.2
unnamed: C11005.2, IC11001.1 (CB)
unnamed: C11002.1, C11003.1, C11004.1, IC11001.4 (EN), IC11001.5 (VIN), L11002.1
unnamed: IC11001.3 (FB), R11004.2, R11005.1
unnamed: C11005.1, IC11001.6 (SW), L11001.2
unnamed: IC13001.2 (RG_1), R13002.1
unnamed: IC13001.3 (RG_2), R13002.2
unnamed: C23002.1, IC13002.4 (-IN), R23001.2
unnamed: C23002.2, IC13002.1 (OUT), U13001.2 (G1)
unnamed: C23003.1, IC13003.4 (-IN), R23002.1
unnamed: C23003.2, IC13003.1 (OUT), U13001.5 (G2)
unnamed: C14006.1, IC14001.1 (CB)
unnamed: C14002.1, C14003.1, C14004.1, C14005.2, IC14001.4 (EN), IC14001.5 (VIN), L14002.1
unnamed: IC14001.3 (FB), R14004.1, R14005.2
unnamed: C14006.2, IC14001.6 (SW), L14001.1
unnamed: IC15001.6 (REF), U18001.1
unnamed: IC15001.2 (RG_1), R15005.1
unnamed: IC15001.3 (RG_2), R15005.2
unnamed: IC17001.2 (RG_1), R17002.1
unnamed: IC17001.3 (RG_2), R17002.2
unnamed: C26002.1, IC17002.4 (-IN), R26001.2
unnamed: C26002.2, IC17002.1 (OUT), U17001.2 (G1)
unnamed: C26003.1, IC17003.4 (-IN), R26002.1
unnamed: C26003.2, IC17003.1 (OUT), U17001.5 (G2)
unnamed: IC36001.6 (REF), U36001.1
unnamed: IC36001.2 (RG_1), R36001.1
unnamed: IC36001.3 (RG_2), R36001.2
unnamed: IC38001.6 (REF), U38001.1
unnamed: IC38001.2 (RG_1), R38001.1
unnamed: IC38001.3 (RG_2), R38001.2
unnamed: J6001.3, R13007.2
unnamed: J6001.11, R6024.2
unnamed: J9001.1, R9002.2
unnamed: J9001.2, R9001.1
unnamed: J13001.4, J13001.5, R7022.2
unnamed: J13001.7, J13001.8, R7023.1
unnamed: J15001.1, R15002.2
unnamed: J15001.2, R15001.1
unnamed: C15007.1, Q15001.3 (G), Q15002.1 (D), Q15002.2 (S), R15004.1, R15006.2
unnamed: C17006.1, Q17001.3 (G), Q17002.1 (D), Q17002.2 (S), R17001.2, R17007.1
unnamed: C19002.1, Q19001.3 (G), Q19002.1 (D), Q19002.2 (S), R19001.2, R19002.1
unnamed: C21002.1, Q21001.3 (G), Q21002.1 (D), Q21002.2 (S), R21001.2, R21002.1
unnamed: C24003.1, Q24001.3 (G), Q24002.1 (D), Q24002.2 (S), R24001.2, R24002.1
unnamed: C27002.1, Q27001.3 (G), Q27002.1 (D), Q27002.2 (S), R27001.2, R27002.1
unnamed: C29002.1, Q29001.3 (G), Q29002.1 (D), Q29002.2 (S), R29001.2, R29002.1
unnamed: C31002.1, Q31001.3 (G), Q31002.1 (D), Q31002.2 (S), R31001.2, R31002.1
unnamed: C33002.1, Q33001.3 (G), Q33002.1 (D), Q33002.2 (S), R33001.2, R33002.1
unnamed: C35002.1, Q35001.3 (G), Q35002.1 (D), Q35002.2 (S), R35001.2, R35002.1
unnamed: C37002.1, Q37001.3 (G), Q37002.1 (D), Q37002.2 (S), R37001.2, R37002.1
unnamed: C39002.1, Q39001.3 (G), Q39002.1 (D), Q39002.2 (S), R39001.2, R39002.1
unnamed: C41002.1, Q41001.3 (G), Q41002.1 (D), Q41002.2 (S), R41001.2, R41002.1
unnamed: C43002.1, Q43001.3 (G), Q43002.1 (D), Q43002.2 (S), R43001.2, R43002.1
unnamed: C45002.1, Q45001.3 (G), Q45002.1 (D), Q45002.2 (S), R45001.2, R45002.1
unnamed: C47002.1, Q47001.3 (G), Q47002.1 (D), Q47002.2 (S), R47001.2, R47002.1
unnamed: R3003.2, R3004.2
unnamed: R7014.1, R7017.2
unnamed: R8006.2, R8007.2
unnamed: R12002.1, R12003.1
unnamed: R12003.2, R12004.2
unnamed: R12005.1, R12006.1
unnamed: R12006.2, R12007.2
unnamed: R12008.2, R12009.1
unnamed: R12010.2, R12011.1
unnamed: R12012.2, R12013.1
unnamed: C7006.2, C7007.2, C7008.2, C7009.2, C7010.2, C7011.2, FB7001.2, R7011.2, R7013.2, R7016.2, R7018.2, T7001.2 (CT_1), T7001.7 (CT_2), U7001.1 (VDD2A), U7001.19 (VDD1A)
unnamed: R7020.1, T7001.10 (NC_3)
unnamed: R7021.2, T7001.15 (NC_6)
unnamed: D7003.3 (TVS1), D7003.6 (TVS2), J13001.3, T7001.11 (RX+)
unnamed: D7003.4 (TVS2), D7003.5 (TVS1), J13001.6, T7001.9 (RX-)
unnamed: D7003.1 (TVS1), D7003.8 (TVS2), J13001.1, T7001.16 (TX+)
unnamed: D7003.2 (TVS2), D7003.7 (TVS1), J13001.2, T7001.14 (TX-)
unnamed: R4001.1, R4006.1, U4001.1 (S1)
unnamed: R4007.2, R4009.1, U4001.4 (S2)
unnamed: R5006.1, R9004.1, U5001.1 (S1)
unnamed: R5009.1, R9006.2, U5001.4 (S2)
unnamed: R7005.2, R7006.2, U7001.11 (CRS_DV/MODE2)
unnamed: R7014.2, U7001.24 (RBIAS)
unnamed: R7001.1, R7002.2, U7001.8 (RXD0/MODE0)
unnamed: R7003.1, R7004.2, U7001.7 (RXD1/MODE1)
unnamed: R7010.2, U7001.10 (RXER/PHYAD0)
unnamed: C7003.2, C7004.2, U7001.6 (VDDCR)
unnamed: U7001.5 (XTAL1/CLKIN), Y7001.3 (CRYSTAL_2)
unnamed: U7001.4 (XTAL2), Y7001.1 (CRYSTAL_1)
unnamed: R7007.1, R7009.2, U7001.14 (~INT/REFCLKO)
unnamed: J8001.1, R8004.2, U8001.3 (+)
unnamed: R12010.1, U12001.1 (S1)
unnamed: R12012.1, U12001.4 (S2)
unnamed: R13006.1, R23001.1, U13001.1 (S1)
unnamed: R13009.1, R23002.2, U13001.4 (S2)
unnamed: C15005.2, R15006.1, U15001.3 (+)
unnamed: R17006.1, R26001.1, U17001.1 (S1)
unnamed: R17009.1, R26002.2, U17001.4 (S2)
unnamed: C17005.2, R17007.2, U17002.3 (+)
unnamed: C19001.2, R19002.2, U19001.3 (+)
unnamed: C21001.2, R21002.2, U21001.3 (+)
unnamed: C24002.2, R24002.2, U24001.3 (+)
unnamed: C27001.2, R27002.2, U27001.3 (+)
unnamed: C29001.2, R29002.2, U29001.3 (+)
unnamed: C31001.2, R31002.2, U31001.3 (+)
unnamed: C33001.2, R33002.2, U33001.3 (+)
unnamed: C35001.2, R35002.2, U35001.3 (+)
unnamed: C37001.2, R37002.2, U37001.3 (+)
unnamed: C39001.2, R39002.2, U39001.3 (+)
unnamed: C41001.2, R41002.2, U41001.3 (+)
unnamed: C43001.2, R43002.2, U43001.3 (+)
unnamed: C45001.2, R45002.2, U45001.3 (+)
unnamed: C47001.2, R47002.2, U47001.3 (+)

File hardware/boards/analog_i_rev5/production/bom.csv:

Designator,Footprint,Quantity,Value,LCSC Part #
"C10001, C10005, C11003, C11006, C12001, C12006",0603,6,0.1uF 50V 0603,C14663
"C10002, C10003, C10004, C11004, C11005, C11008, C12002, C12003, C12008, C17008, C20001, C24001, C28001, C3001, C3002, C3003, C8003",0805,17,10uF 50V 0805,C440198
"C10006, C11007, C12007",0805,3,2.2uF 50V 0805,C377773
"C11001, C14001, C18001, C22001, C6023, C6025",0402,6,10nF,C15195
"C11002, C13004, C13007, C13010, C14002, C15004, C15006, C15008, C17004, C17007, C17009, C17010, C18002, C19003, C21003, C22002, C24004, C27003, C29003, C31003, C33003, C35003, C36001, C37003, C38001, C39003, C40001, C4004, C4007, C4010, C41003, C42001, C43003, C44001, C45003, C46001, C47003, C48001, C49001, C50001, C5004, C5007, C5008, C5009, C5010, C51001, C52001, C53001, C54001, C55001, C56001, C57001, C58001, C6021, C6022, C6024, C6026, C6027, C6028, C6029, C6030, C6031, C6032, C6033, C6034, C6036, C6037, C6038, C6039, C6041, C6043, C6048, C6050, C7005, C7006, C7007, C7008, C7010, C7011, C8005, C9004, C9006",0402,82,0.1uF,
"C13001, C13003, C17001, C17003, C4001, C4003, C5001, C5003",0402,8,1nF,
"C13002, C17002, C4002, C5002",0402,4,10nF,
"C15001, C15003, C9001, C9003",0402,4,2.2uF,
"C15002, C9002",0402,2,1uF,
"C15005, C15007, C17005, C17006, C19001, C19002, C21001, C21002, C24002, C24003, C27001, C27002, C29001, C29002, C31001, C31002, C33001, C33002, C35001, C35002, C37001, C37002, C39001, C39002, C41001, C41002, C43001, C43002, C45001, C45002, C47001, C47002",0402,32,10nF C0G 5%,C3855387
"C5012, C6035, C6040, C6049, C6051, C7009, C8006",0603,7,10uF,
"C6001, C6002, C6003, C6004, C6005, C6006, C6007, C6008, C6009, C6010, C6011, C6012, C6013, C6016, C6017, C6018, C6019, C6020, C7004",0402,19,1uF 0402,C52923
"C7001, C7002",0402,2,5.6pF 0402,C258497
C7003,0402,1,470pF 0402,C363540
C7012,0402,1,4.7nF,
C8001,0603,1,0.1uF 0603,
"D13001, D17001, D4001, D5001",D_SMA,4,D_Schottky,C22452
"D23001, D26001, D4002, D5002, D6005, D8001, D8002, D9001",D_SOD-323,8,BZT52C3V3,C2112
"D48001, D49001, D50001, D51001, D52001, D55001, D56001, D57001, D58001",D_SOD-323,9,BZT52C5V6S,C5184420
"D6001, D6002, D6003, D6004, D7001, D7002",0603,6,Purple LED,C7371898
D7003,SOIC-8_3.9x4.9mm_P1.27mm,1,CDNBS08-SLVU2.8-4,
FB7001,0805,1,GZ2012D601TF,C1017
"IC10001, IC11002, IC12001",SOT-23-6,3,TPS560430XDBVR,
"IC11001, IC13001, IC14001, IC15001, IC17001, IC18001, IC22001, IC36001, IC38001, IC40001, IC4001, IC42001, IC44001, IC46001, IC5001, IC53001, IC54001, IC8001, IC9001",SOIC127P600X175-8N,19,INA826AIDR,C38433
"IC13002, IC13003, IC17002, IC17003, IC4002, IC4003, IC5002, IC5003",SOT-23-5,8,TLV333IDBVR,
"IC17004, IC20001, IC24001, IC28001, IC3001, IC3002, IC3003",SOIC127P600X175-8N,7,BD42540FJ-CE2,C308591
IC5004,SOT95P280X145-6N,1,REF35102QDBVR,
IC6001,QFP50P2200X2200X160-144N,1,STM32H743ZIT6,C114408
"J15001, J9001",AM-K-PCB,2,AM-K-PCB,C9900157061
"J3001, J3003, J3004, J3006",KF141V-2.54-12P,4,Screw_Terminal_01x12,C475123
"J3002, J3005",KF141V-2.54-10P,2,Screw_Terminal_01x10,C475122
J6001,PinHeader_2x07_P1.27mm_Vertical_SMD,1,Conn_02x07_Odd_Even,C3975190
J7001,63391601,1,6339160-1,C125076
J8001,BarrelJack_Horizontal,1,Barrel_Jack PJ-202BH,C3094841
L10001,INDPM4040X300N,1,12uH FNR4030S120MT,C167880
L11001,INDPM4040X300N,1,18uH  FNR4030S180MT, C167882
L12001,INDPM4040X300N,1,33uH  FNR4020S330MT,C167840
"R10001, R11005, R12002",0603,3,22.1k 0603,C25961
R10002,0603,1,51k 0603,C23196
"R10003, R11003, R12003",0805,3,1R 0805,C25271
"R11001, R14001, R18001, R22001",0402,4,200R,C25087
"R11002, R14002, R18002, R22002, R36001",0603,5,RNCF0603TKY75R0 75R 0.01% 5ppm/C,C2482496
R11004,0603,1,88.7k 0603,C203875
R12001,0603,1,243k 0603,C23351
"R13002, R15005, R17002, R38001, R40002, R4002, R42002, R5002, R9005",0603,9,RNCF0603TKY2K00 2k 0.01% 5ppm/C,C346578
"R13003, R17003, R4003, R5003",0805,4,300,
"R13004, R13005, R17004, R17005, R4004, R4005, R5004, R5005",0402,8,10k 1%,
"R13006, R13009, R17006, R17009, R40001, R4006, R4009, R42001, R5006, R5009",0603,10,RNCF0603TKW10K0 10k 0.01% 5ppm/C,C2482678
"R13007, R6024",0402,2,100R 0402,C25076
"R15001, R9001",0402,2,10,C25077
"R15002, R9002",0402,2,10,
"R15003, R36002, R38002, R44001, R46001, R48002, R49002, R50002, R51002, R52002, R53001, R54001, R55001, R56001, R57001, R58001, R9003",0402,17,1M,
"R15004, R15006, R37001, R37002",0402,4,100k 1%,C25741
"R17001, R17007, R19001, R19002, R39001, R39002",0402,6,10k 1%,C25744
"R21001, R21002, R24001, R24002, R27001, R27002, R29001, R29002, R31001, R31002, R33001, R33002, R35001, R35002, R41001, R41002, R43001, R43002, R45001, R45002, R47001, R47002",0402,22,3.3k 1%,C25890
R3001,0603,1,PTS060301B100RP100,C141518
"R48001, R49001, R50001, R51001, R52001, R55002, R56002, R57002, R58002",0805,9,49.9,C17720
"R6001, R6002, R6003, R6004, R6005, R6006, R6007, R6008, R6009, R6010, R6011, R6012, R6013, R6016, R6017, R6018, R6019, R6020",0603,18,10R 0603,C22859
"R6021, R6022, R6023, R6025, R6026, R6027, R6028, R6029, R6030, R7002, R7004, R7006, R7009, R7010, R7012, R7019, R8006, R8007",0402,18,10k,C25744
"R7001, R7003, R7005, R7007",0402,4,33R,C25105
"R7008, R7015, R8005",0402,3,1.5k,C25867
"R7011, R7013, R7016, R7018",0402,4,49.9,C25120
R7014,0402,1,12k,C25752
R7017,0402,1,100R,C25076
"R7020, R7021, R7022, R7023",0603,4,75,C23242
R7024,0402,1,1M,C26083
R8004,2512,1,MRF6432(2512)LR006FTS 0.006 1%,C76239
S6001,TS1187ABAB,1,TS-1187A-B-A-B,C318884
T7001,SOIC127P940X622-16N,1,H1102NLT, C18584
TP7001,TestPoint_Pad_D1.0mm,1,TestPoint_+12V,
TP7002,TestPoint_Pad_D1.0mm,1,TestPoint_+5V,
TP7003,TestPoint_Pad_D1.0mm,1,TestPoint_+2V5,
TP7004,TestPoint_Pad_D1.0mm,1,TestPoint_+3V3,
TP7005,TestPoint_Pad_D1.0mm,1,TestPoint_+1V024,
TP8002,TestPoint_Pad_D1.0mm,1,TestPoint_GND_1,
"U13001, U17001, U4001, U5001",SOT-363_SC-70-6,4,NTJD4001NT1G,C190019
"U15001, U17002, U19001, U21001, U24001, U27001, U29001, U31001, U33001, U35001, U37001, U39001, U41001, U43001, U45001, U47001",SOT-23-5,16,OPA333xxDBV,
"U48001, U49001, U50001, U51001, U52001, U55001, U56001, U57001, U58001",SOT-23-5,9,74LVC1G17,C7836
U6002,SOIC-8_3.9x4.9mm_P1.27mm,1,ADR4525,C403914
U7001,VQFN-24-1EP_4x4mm_P0.5mm_EP2.5x2.5mm_ThermalVias,1,LAN8742A,
U8001,SOT-23-6,1,INA181A2,C2058784
Y6001,Crystal_SMD_3225-4Pin_3.2x2.5mm,1,SiT1602BI-21-33S-48.000000,C1198900
Y7001,Crystal_SMD_2016-4Pin_2.0x1.6mm,1,NX2016SA-25.000M-STD-CZS-1,C843258
